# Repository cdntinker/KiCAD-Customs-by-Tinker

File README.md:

## A better USB-C footprint

* **USB_C.kicad_sym**
* **USB_C.kicad_mod**

A much stronger and easier routed footprint than typical.

Combines the data lines.  (This may be handy since most installations of a USB-C connector include bridging these together in your design...)

**tests 2.kicad_pro** is an example of usage for this footprint.

### a version without the combined data lines

* **USB_C(sd).kicad_mod**

## A handy footprint for power output.

* **USB_A-C_2.0_XT30.kicad_sym**
* **USB_A+C+XT30.kicad_mod**

Allows for USB-A, USB-C or an XT30 connector.

USB-A includes the data lines so it will work for a QC source.

USB-C includes the data lines AND the CC & SBU lines so it will work for a QC or PD source. (as well as whatever the SBU pins are actually for... Closest I've managed to find to a useful description is as Agnd & Mic in "Audio Adapter Accessory Mode".)

> [!NOTE]
> the origin of this footprint is now where the centre line meets the board edge.

> [!TIP]
> You can select the model for 3D renders by going into the footprint properties after placing it on your PCB, selecting the "3d Models" tab & enabling whichever model you like.

**tests.kicad_pro** is an example of usage for this footprint.

## Solder Jumpers that actually fit.

* **tinySJ-Open.kicad_mod**
* **tinySJ-Bridged.kicad_mod**

The solder jumper footprints that come standard with KiCAD are handy, but massive.

These are not massive.

**TinySJ.kicad_pro** is an example of usage for this footprint.

## A pogo-pin connection point for UPDI programming

* **UPDI_connection.kicad_sym**
* **UPDI.kicad_mod**

**UPDI.kicad_pro** is an example of usage for this footprint.

& the [tool](https://github.com/cdntinker/Benchtop-Modular-Power-Strip/tree/main/Hardware/Tool%20-%20ATTiny%20Module%20Flasher) that uses this footprint:

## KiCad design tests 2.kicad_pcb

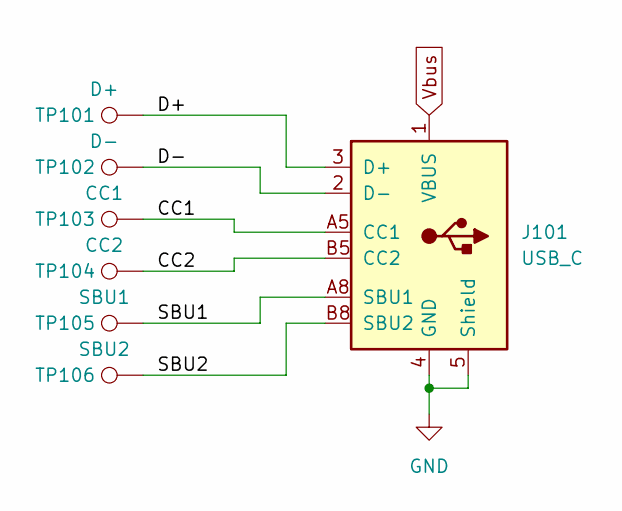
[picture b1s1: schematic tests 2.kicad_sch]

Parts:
J101: USB_C; LCSC A-(C6389922) C-(C2765186) XT30-(C291328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
TP101: D+; TestPoint_THTPad_D1.0mm_Drill0.5mm
TP102: D-; TestPoint_THTPad_D1.0mm_Drill0.5mm
TP103: CC1; TestPoint_THTPad_D1.0mm_Drill0.5mm
TP104: CC2; TestPoint_THTPad_D1.0mm_Drill0.5mm
TP105: SBU1; TestPoint_THTPad_D1.0mm_Drill0.5mm
TP106: SBU2; TestPoint_THTPad_D1.0mm_Drill0.5mm

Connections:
/CC1: J101.A5 (CC1), TP103.1
/CC2: J101.B5 (CC2), TP104.1
/D+: J101.3 (D+), TP101.1
/D-: J101.2 (D-), TP102.1
/SBU1: J101.A8 (SBU1), TP105.1
/SBU2: J101.B8 (SBU2), TP106.1
GND: J101.4 (GND), J101.5 (Shield)
Vbus: J101.1 (VBUS)

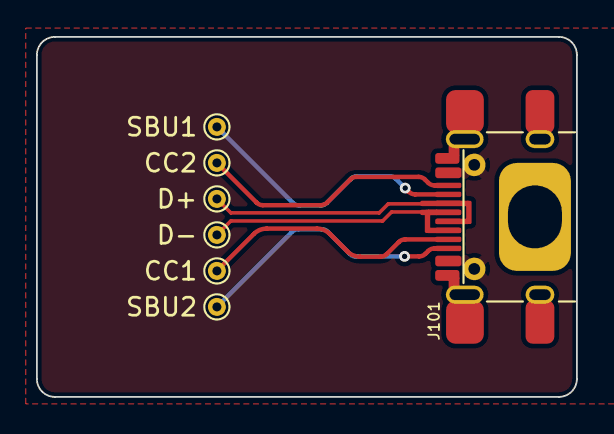
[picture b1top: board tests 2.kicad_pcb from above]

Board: 2 copper layers, 30.0 x 20.0 mm, 7 parts (0 on the bottom side), 7 nets.

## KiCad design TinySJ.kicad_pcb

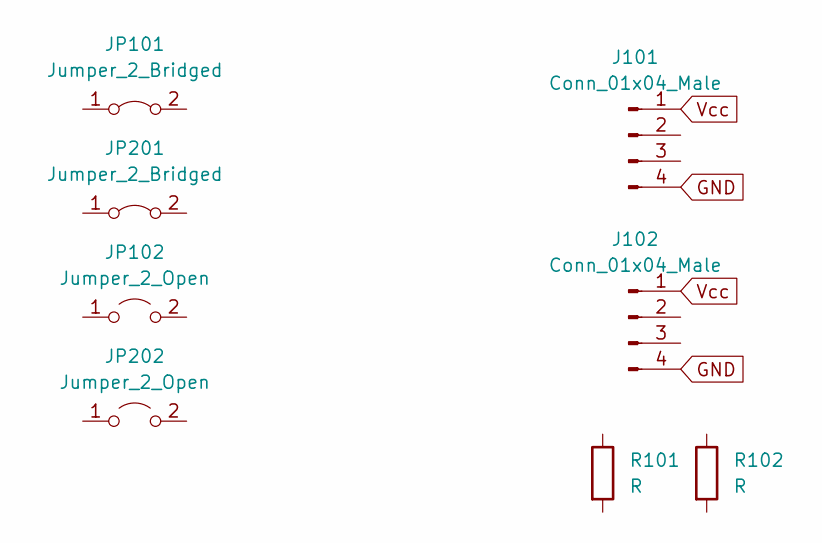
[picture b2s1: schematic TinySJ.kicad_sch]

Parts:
J101: Conn_01x04_Male; PinHeader_1x04_P2.54mm_Vertical
J102: Conn_01x04_Male; PinHeader_1x04_P1.27mm_Vertical
JP101: Jumper_2_Bridged; tinySJ-Bridged
JP102: Jumper_2_Open; tinySJ-Open
JP201: Jumper_2_Bridged; SolderJumper-2_P1.3mm_Bridged_RoundedPad1.0x1.5mm
JP202: Jumper_2_Open; SolderJumper-2_P1.3mm_Open_RoundedPad1.0x1.5mm
R101: R; R_0603_1608Metric
R102: R; R_0805_2012Metric

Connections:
GND: J101.4, J102.4
Vcc: J101.1, J102.1

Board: 2 copper layers, 8 parts (0 on the bottom side), 2 nets, no tracks yet.

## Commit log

2024-04-06 Moved footprint origin & added info to README.md
2024-04-06 fixed oops with the 3D model placements...
2024-04-11 Added tiny Solder Jumpers
2024-04-11 & renamed repo
2024-04-13 Better tinySJ example board...
2024-04-13 Added UPDI footprint & symbol
2024-05-05 Added straight-up USB-C But needs symbol...
2024-05-05 now with symbol too
2024-05-05 Tweaking the USB-C footprint
2024-05-05 More USB-C tweaking...
2024-05-05 A bit more USB-C tweaking
2024-05-05 README updates
2024-05-05 corrected miss-labelled pins in USB_C(sd)
